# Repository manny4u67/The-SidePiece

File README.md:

# The SidePiece
 The only sidepiece you should have

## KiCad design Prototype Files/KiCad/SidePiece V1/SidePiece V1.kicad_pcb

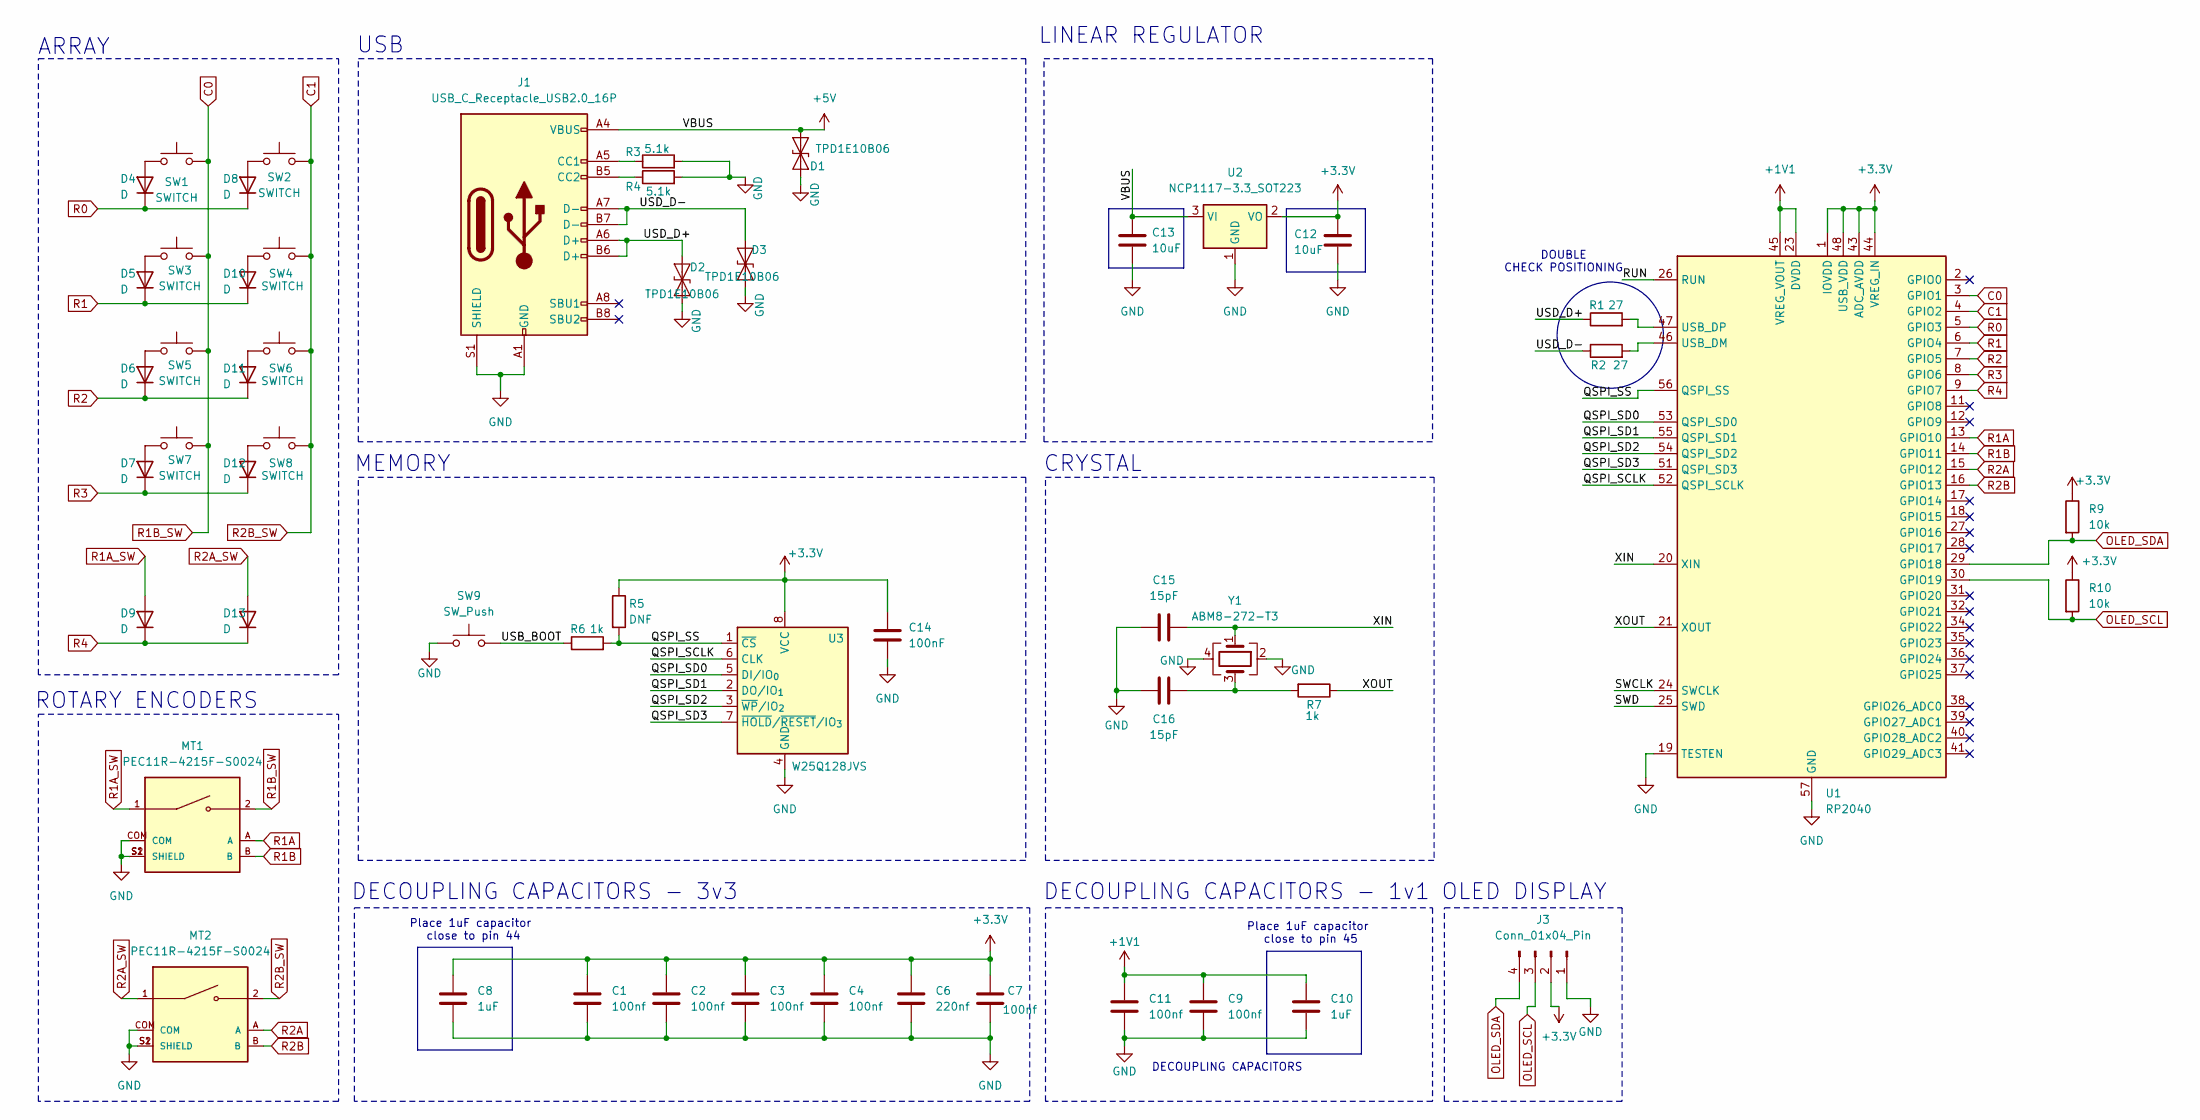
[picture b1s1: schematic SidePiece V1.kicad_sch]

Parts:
C1, C2, C3, C4, C7, C9, C11: 100nf; C_0402_1005Metric
C6: 220nf; C_0402_1005Metric
C8, C10: 1uF; C_0402_1005Metric
C12, C13: 10uF; C_0805_2012Metric
C14: 100nF; C_0603_1608Metric
C15, C16: 15pF; C_0603_1608Metric
D1, D2, D3: TPD1E10B06; D_SOD-523
D4, D5, D6, D7, D8, D9, D10, D11, D12, D13: D; D_0603_1608Metric
J1: USB_C_Receptacle_USB2.0_16P; USB_C_Receptacle_GCT_USB4105-xx-A_16P_TopMnt_Horizontal
J3: Conn_01x04_Pin; OLED
MT1, MT2: PEC11R-4215F-S0024; XDCR_PEC11R-4215F-S0024; PARTREV Rev. 09/19
R1, R2: 27; R_0603_1608Metric
R3, R4: 5.1k; R_0603_1608Metric
R5: DNF; R_0603_1608Metric
R6: 1k; C_0603_1608Metric
R7: 1k; R_0603_1608Metric
R9, R10: 10k; R_0402_1005Metric
SW1, SW2, SW3, SW4, SW5, SW6, SW7, SW8: SWITCH; Kailh_socket_PG1350
SW9: SW_Push; SW_SPST_PTS810
U1: RP2040; QFN-56-1EP_7x7mm_P0.4mm_EP3.2x3.2mm
U2: NCP1117-3.3_SOT223; SOT-223-3_TabPin2
U3: W25Q128JVS; SOIC-8_5.3x5.3mm_P1.27mm
Y1: ABM8-272-T3; Crystal_SMD_3225-4Pin_3.2x2.5mm

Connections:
+1V1: C9.1, C10.1, C11.1, U1.23 (DVDD), U1.45 (VREG_VOUT), U1.50 (DVDD)
+3.3V: C1.1, C2.1, C3.1, C4.1, C6.1, C7.1, C8.1, C12.1, C14.1, J3.2, R5.1, R9.1, R10.1, U1.1 (IOVDD), U1.10 (IOVDD), U1.22 (IOVDD), U1.33 (IOVDD), U1.42 (IOVDD), U1.43 (ADC_AVDD), U1.44 (VREG_IN), U1.48 (USB_VDD), U1.49 (IOVDD), U2.2 (VO), U3.8 (VCC)
+5V: C13.1, D1.1 (A1), J1.A4 (VBUS), J1.A9 (VBUS), J1.B4 (VBUS), J1.B9 (VBUS), U2.3 (VI)
/QSPI_SCLK: U1.52 (QSPI_SCLK), U3.6 (CLK)
/QSPI_SD0: U1.53 (QSPI_SD0), U3.5 (DI/IO_{0})
/QSPI_SD1: U1.55 (QSPI_SD1), U3.2 (DO/IO_{1})
/QSPI_SD2: U1.54 (QSPI_SD2), U3.3 (~WP/IO_{2})
/QSPI_SD3: U1.51 (QSPI_SD3), U3.7 (~HOLD/~RESET/IO_{3})
/QSPI_SS: R5.2, R6.2, U1.56 (QSPI_SS), U3.1 (~CS)
/RUN: U1.26 (RUN)
/SWCLK: U1.24 (SWCLK)
/SWD: U1.25 (SWD)
/USB_BOOT: R6.1, SW9.2
/USD_D+: D2.1 (A1), J1.A6 (D+), J1.B6 (D+), R1.1
/USD_D-: D3.1 (A1), J1.A7 (D-), J1.B7 (D-), R2.1
/XIN: C15.2, U1.20 (XIN), Y1.1
/XOUT: R7.1, U1.21 (XOUT)
C0: MT1.2, SW1.2, SW3.2, SW5.2, SW7.2, U1.3 (GPIO1)
C1: MT2.2, SW2.2, SW4.2, SW6.2, SW8.2, U1.4 (GPIO2)
GND: C1.2, C2.2, C3.2, C4.2, C6.2, C7.2, C8.2, C9.2, C10.2, C11.2, C12.2, C13.2, C14.2, C15.1, C16.1, D1.2 (A2), D2.2 (A2), D3.2 (A2), J1.A1 (GND), J1.A12 (GND), J1.B1 (GND), J1.B12 (GND), J1.S1 (SHIELD), J3.1, MT1.COM, MT1.S1 (SHIELD), MT1.S2 (SHIELD), MT2.COM, MT2.S1 (SHIELD), MT2.S2 (SHIELD), R3.2, R4.2, SW9.1, U1.19 (TESTEN), U1.57 (GND), U2.1 (GND), U3.4 (GND), Y1.2, Y1.4
unnamed: C16.2, R7.2, Y1.3
unnamed: D4.2 (A), SW1.1
unnamed: D5.2 (A), SW3.1
unnamed: D6.2 (A), SW5.1
unnamed: D7.2 (A), SW7.1
unnamed: D8.2 (A), SW2.1
unnamed: D10.2 (A), SW4.1
unnamed: D11.2 (A), SW6.1
unnamed: D12.2 (A), SW8.1
unnamed: J1.A5 (CC1), R3.1
unnamed: J1.B5 (CC2), R4.1
unnamed: R2.2, U1.46 (USB_DM)
unnamed: R1.2, U1.47 (USB_DP)
OLED_SCL: J3.3, R10.2, U1.30 (GPIO19)
OLED_SDA: J3.4, R9.2, U1.29 (GPIO18)
R0: D4.1 (K), D8.1 (K), U1.5 (GPIO3)
R1: D5.1 (K), D10.1 (K), U1.6 (GPIO4)
R1A: MT1.A, U1.13 (GPIO10)
R1A_SW: D9.2 (A), MT1.1
R1B: MT1.B, U1.14 (GPIO11)
R2: D6.1 (K), D11.1 (K), U1.7 (GPIO5)
R2A: MT2.A, U1.15 (GPIO12)
R2A_SW: D13.2 (A), MT2.1
R2B: MT2.B, U1.16 (GPIO13)
R3: D7.1 (K), D12.1 (K), U1.8 (GPIO6)
R4: D9.1 (K), D13.1 (K), U1.9 (GPIO7)

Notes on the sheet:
DECOUPLING CAPACITORS
DOUBLE CHECK POSITIONING
MEMORY
ARRAY
CRYSTAL
DECOUPLING CAPACITORS - 1v1
LINEAR REGULATOR
USB
ROTARY ENCODERS
Place 1uF capacitor close to pin 45
OLED DISPLAY
Place 1uF capacitor close to pin 44
DECOUPLING CAPACITORS - 3v3

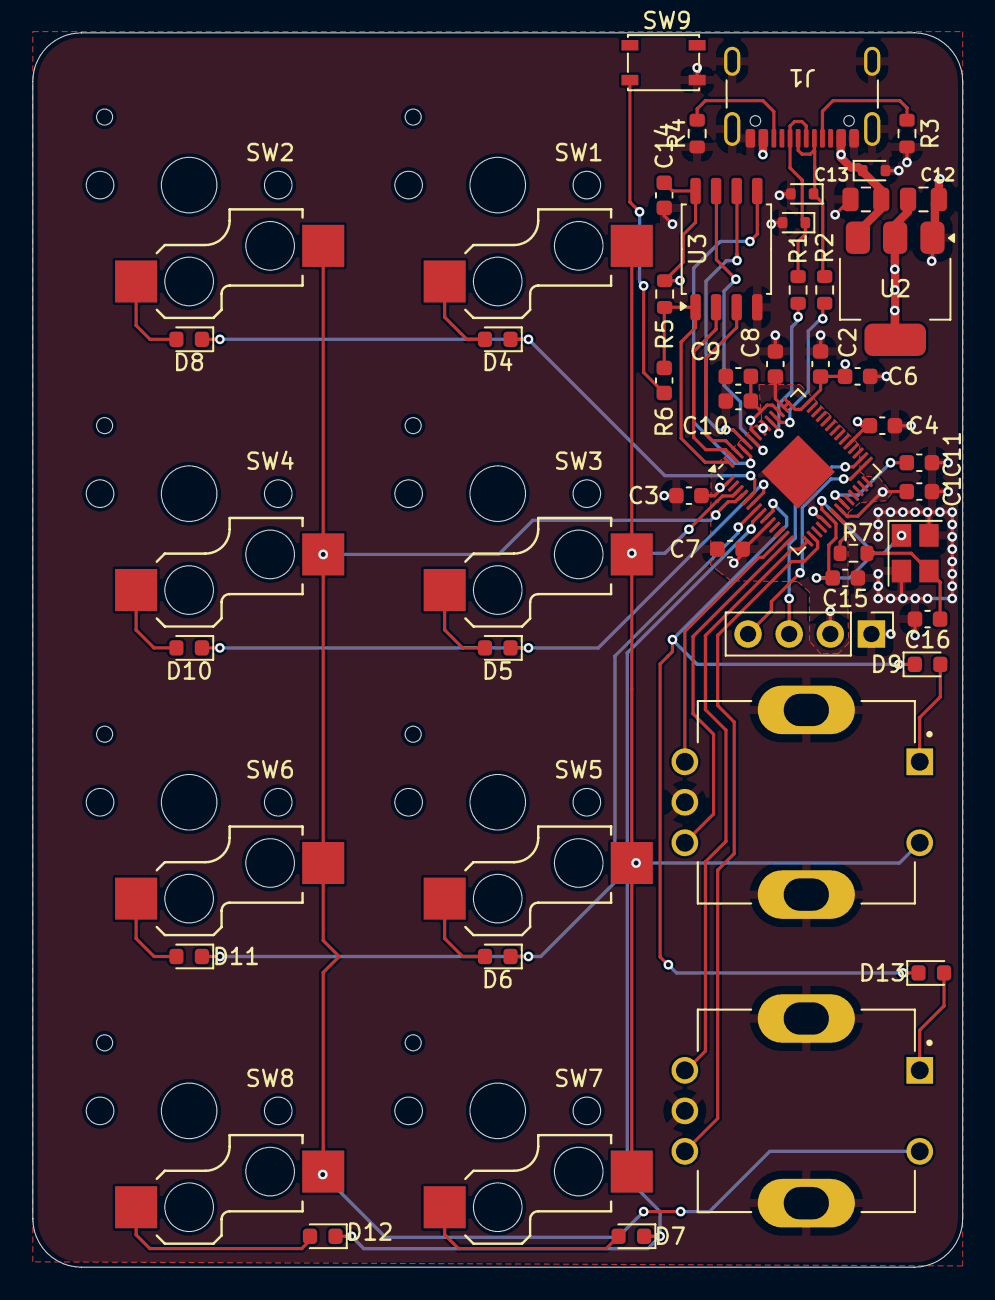
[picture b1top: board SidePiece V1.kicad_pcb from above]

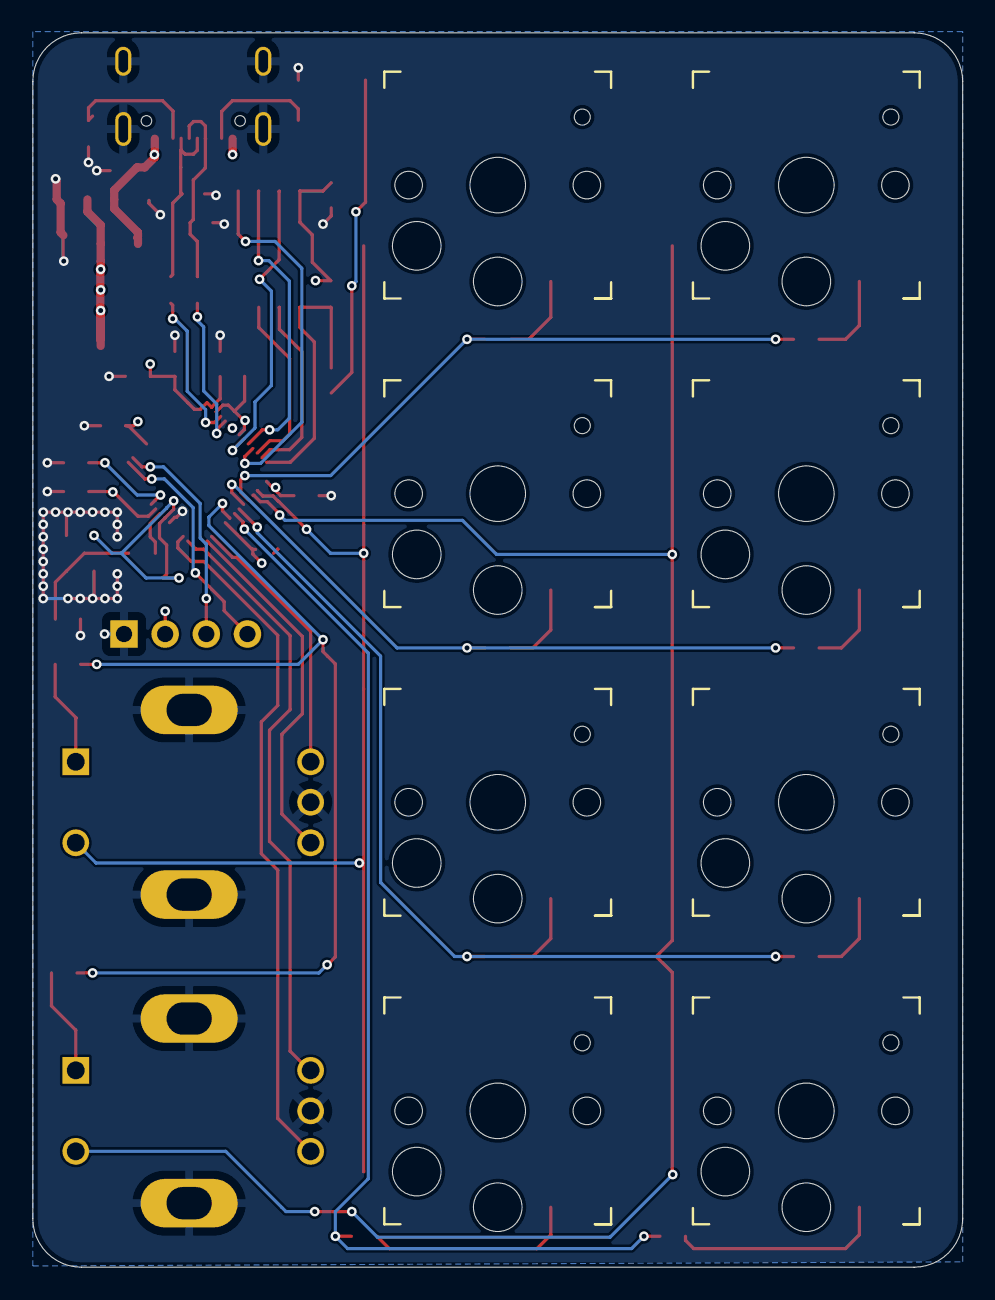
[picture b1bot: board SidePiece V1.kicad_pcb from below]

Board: 4 copper layers, 57.4 x 76.2 mm, 52 parts (8 on the bottom side), 43 nets.

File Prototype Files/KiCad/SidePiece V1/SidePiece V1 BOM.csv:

"Reference","Qty","Value","DNP","Exclude from BOM","Exclude from Board","Footprint","Datasheet"
"C1,C2,C3,C4,C5,C6,C7,C9,C11","9","100nf","","","","Capacitor_SMD:C_0603_1608Metric","~"
"C8,C10","2","1uF","","","","Capacitor_SMD:C_0603_1608Metric","~"
"C12,C13","2","10uF","","","","Capacitor_SMD:C_0805_2012Metric","~"
"C14","1","100nF","","","","Capacitor_SMD:C_0603_1608Metric","~"
"C15,C16","2","15pF","","","","Capacitor_SMD:C_0603_1608Metric","~"
"D1,D2,D3","3","TPD1E10B06","","","","Diode_SMD:D_SOD-523","https://www.onsemi.com/pub/Collateral/ESD9B-D.PDF"
"D4,D5,D6,D7,D8,D9,D10,D11,D12,D13","10","D","","","","Diode_SMD:D_0603_1608Metric","~"
"J1","1","USB_C_Receptacle_USB2.0_16P","","","","Connector_USB:USB_C_Receptacle_GCT_USB4105-xx-A_16P_TopMnt_Horizontal","https://www.usb.org/sites/default/files/documents/usb_type-c.zip"
"J3","1","Conn_01x04_Pin","","","","1_my_custom_libary_pretty:OLED","~"
"MT1,MT2","2","PEC11R-4215F-S0024","","","","1_my_custom_libary_pretty:XDCR_PEC11R-4215F-S0024",""
"R1,R2","2","27","","","","Resistor_SMD:R_0603_1608Metric","~"
"R3,R4","2","5.1k","","","","Resistor_SMD:R_0603_1608Metric","~"
"R5","1","DNF","","","","Resistor_SMD:R_0603_1608Metric","~"
"R6","1","1k","","","","Capacitor_SMD:C_0603_1608Metric","~"
"R7","1","1k","","","","Resistor_SMD:R_0603_1608Metric","~"
"SW1,SW2,SW3,SW4,SW5,SW6,SW7,SW8","8","SWITCH","","","","1_my_custom_libary_pretty:Kailh_socket_PG1350","https://omronfs.omron.com/en_US/ecb/products/pdf/en-b3fs.pdf"
"SW9","1","SW_Push","","","","1_my_custom_libary_pretty:SW_SPST_PTS810","~"
"U1","1","RP2040","","","","Package_DFN_QFN:QFN-56-1EP_7x7mm_P0.4mm_EP3.2x3.2mm","https://datasheets.raspberrypi.com/rp2040/rp2040-datasheet.pdf"
"U2","1","NCP1117-3.3_SOT223","","","","Package_TO_SOT_SMD:SOT-223-3_TabPin2","http://www.onsemi.com/pub_link/Collateral/NCP1117-D.PDF"
"U3","1","W25Q128JVS","","","","Package_SO:SOIC-8_5.3x5.3mm_P1.27mm","https://www.winbond.com/resource-files/w25q128jv_dtr%20revc%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"
"Y1","1","ABM8-272-T3","","","","Crystal:Crystal_SMD_3225-4Pin_3.2x2.5mm","~"

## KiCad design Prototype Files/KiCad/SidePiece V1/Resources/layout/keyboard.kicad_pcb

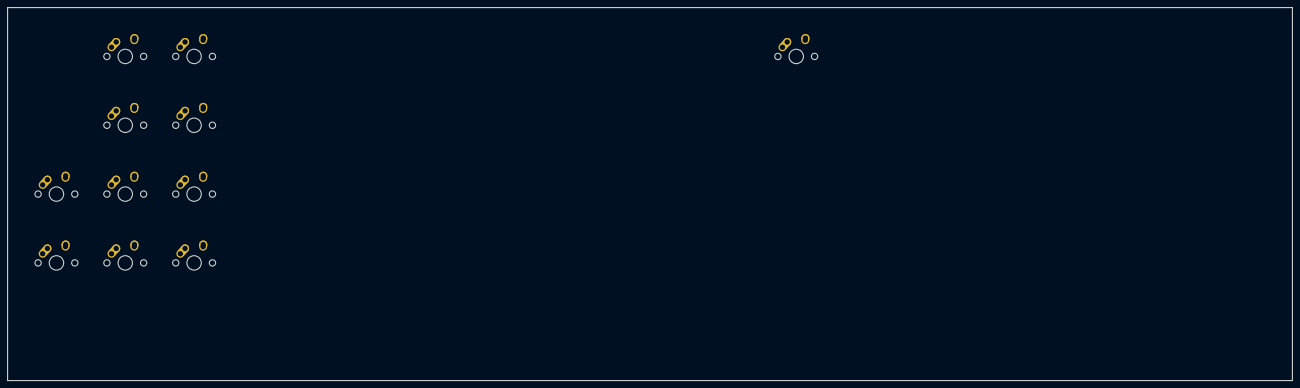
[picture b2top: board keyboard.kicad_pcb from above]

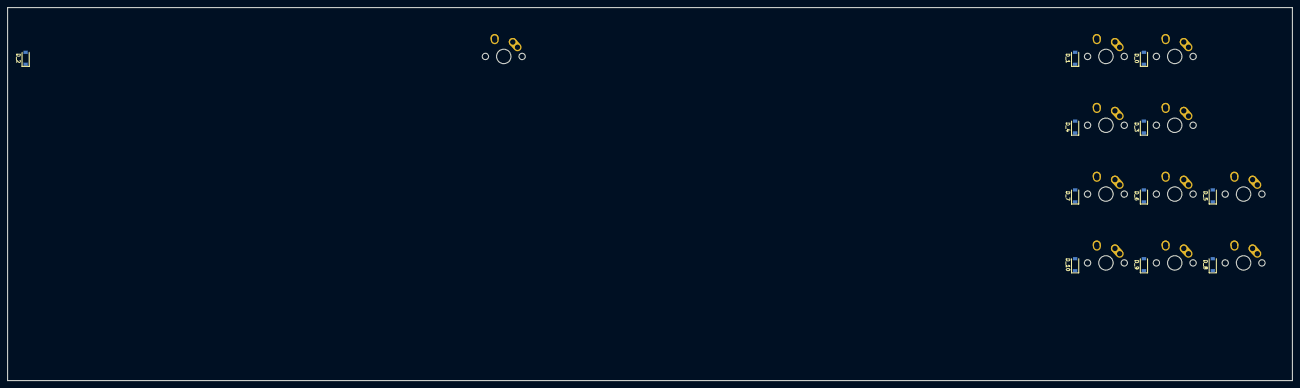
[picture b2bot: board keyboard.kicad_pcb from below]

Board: 2 copper layers, 355.7 x 103.2 mm, 22 parts (11 on the bottom side), 17 nets, no tracks yet.

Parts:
D_0, D_1, D_2, D_3, D_4, D_5, D_6, D_7, D_8, D_9, D_10: D; D_SOD-123
K_0, K_1, K_3, K_4, K_5, K_6, K_7, K_8, K_9, K_10: KEYSW; MX-1U-NoLED
K_2: KEYSW; MX-14U-NoLED

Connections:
unnamed: D_0.2, K_0.2
unnamed: D_1.2, K_1.2
unnamed: D_2.2, K_2.2
unnamed: D_3.2, K_3.2
unnamed: D_4.2, K_4.2
unnamed: D_5.2, K_5.2
unnamed: D_6.2, K_6.2
unnamed: D_7.2, K_7.2
unnamed: D_8.2, K_8.2
unnamed: D_9.2, K_9.2
unnamed: D_10.2, K_10.2
col0: K_5.1, K_8.1
col1: K_0.1, K_3.1, K_6.1, K_9.1
col2: K_1.1, K_4.1, K_7.1, K_10.1
row0: D_0.1, D_1.1
row1: D_3.1, D_4.1
row2: D_2.1, D_5.1, D_6.1, D_7.1, D_8.1, D_9.1, D_10.1

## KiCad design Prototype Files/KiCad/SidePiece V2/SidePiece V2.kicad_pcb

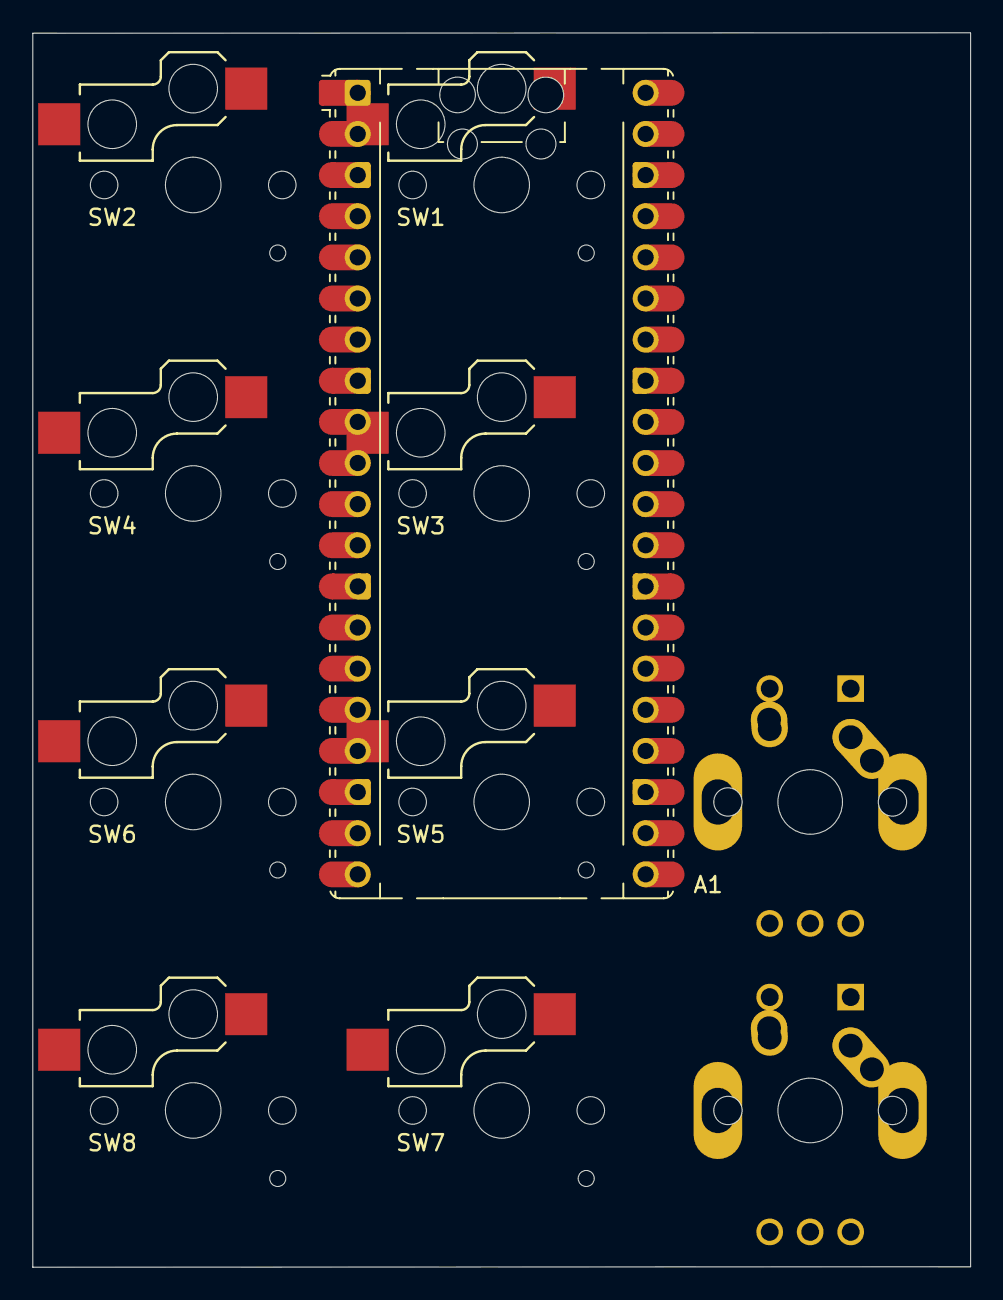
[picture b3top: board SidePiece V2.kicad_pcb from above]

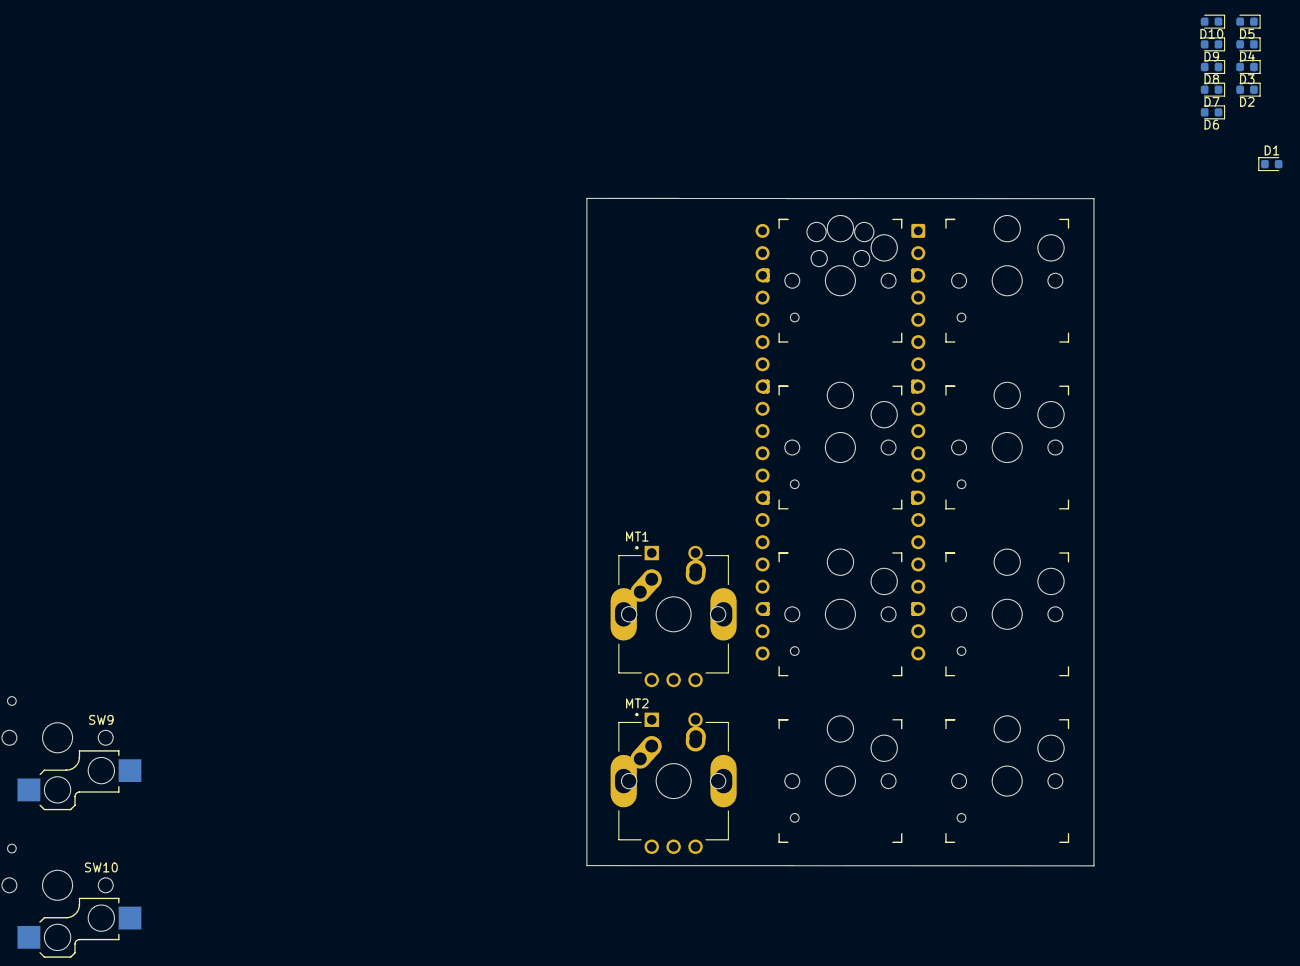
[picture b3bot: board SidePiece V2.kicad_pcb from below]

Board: 4 copper layers, 57.9 x 76.2 mm, 25 parts (22 on the bottom side), 21 nets, no tracks yet.

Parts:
A1: RaspberryPi_Pico; RaspberryPi_Pico_Common_Unspecified
D1, D2, D3, D4, D5, D6, D7, D8, D9, D10: D; D_0603_1608Metric
K_5, K_8: KEYSW; MX-1U-NoLED
MT1, MT2: PEC11R-4215F-S0024; XDCR_PEC11R-4215F-S0024
SW1, SW2, SW3, SW4, SW5, SW6, SW7, SW8, SW9, SW10: SWITCH; Kailh_socket_PG1350

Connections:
C0: A1.2 (GPIO1), SW2.2, SW4.2, SW6.2, SW8.2, SW9.2
C1: A1.4 (GPIO2), SW1.2, SW3.2, SW5.2, SW7.2, SW10.2
unnamed: A1.3 (GND), A1.8 (GND), A1.13 (GND), A1.18 (GND), A1.23 (GND), A1.28 (GND), A1.38 (GND)
unnamed: D1.2 (A), SW2.1
unnamed: D2.2 (A), SW1.1
unnamed: D3.2 (A), SW4.1
unnamed: D4.2 (A), SW3.1
unnamed: D5.2 (A), SW6.1
unnamed: D6.2 (A), SW5.1
unnamed: D7.2 (A), SW8.1
unnamed: D8.2 (A), SW7.1
unnamed: D9.2 (A), SW9.1
unnamed: D10.2 (A), SW10.1
unnamed: MT1.S1 (SHIELD), MT1.S2 (SHIELD)
unnamed: MT2.S1 (SHIELD), MT2.S2 (SHIELD)
R0: A1.5 (GPIO3), D1.1 (K), D2.1 (K)
R1: A1.6 (GPIO4), D3.1 (K), D4.1 (K)
R2: A1.7 (GPIO5), D5.1 (K), D6.1 (K)
R3: A1.9 (GPIO6), D7.1 (K), D8.1 (K)
R4: A1.10 (GPIO7), D9.1 (K), D10.1 (K)
col0: K_5.1, K_8.1

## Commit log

2025-03-27 Functional MacroPad Files For QMK Compilation
    No VIA configuration as of now
2025-03-29 Updated To Add Via Compatibility
2025-04-02 Files for PCB Design
2025-04-02 Updates for qmk testing
2025-04-04 Keyboard is now QMK and VIA compatible
2025-04-04 Rotary Encoder Functional
2025-04-05 Corrected code where via was pointing to the same
2025-04-18 PCB files
2025-05-05 PCB Stuff
2025-06-02 KiCad Files
2025-06-28 Mad corrections to nets
